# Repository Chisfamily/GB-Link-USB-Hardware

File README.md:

# GB-LINK-USB

**An open-source USB adapter for the Game Boy Link Cable.**

| Top view — v1.4 | Bottom view — v1.4 |
| --- | --- |
|  |  |

*The renders show the current **v1.4** board; the bottom silkscreen reads `GB-Link HW Rev 1.4` with date `20261007`.*

GB-LINK-USB is an RP2040-based hardware adapter that connects original Nintendo
Game Boy, Game Boy Color, and Game Boy Advance systems to a computer over USB.
Together with the open-source
[GBLink-Firmware](https://github.com/GB-Link/GBLink-Firmware), it brings modern
connectivity and community-built tools to original Game Boy hardware.

This hardware was developed with reference to the
[GB-Link-USB-DIY](https://github.com/GB-Link/GB-Link-USB-DIY) project and is
designed to be compatible with the GBLink firmware and its web-based clients.

> [!IMPORTANT]
> The board documented here is hardware **v1.4**. It works with **Game Boy Color
> and Game Boy Advance** (and the original Game Boy) over the Link cable, and it
> adapts the Link-interface power automatically: there is no voltage-selection
> jumper, DIP switch or mechanical switch anywhere on the board.

> [!NOTE]
> GB-LINK-USB is the hardware interface. Available features depend on the
> installed firmware, client software, selected cable, game, and firmware
> version.

## What Can It Do?

With compatible firmware and client software, GB-LINK-USB can provide the
following functions:

| Mode | Description |
| --- | --- |
| **GBA online link** | Bridges two original Game Boy Advance systems over the Internet through a compatible client and server. |
| **Pokémon Gen III trade emulation** | Emulates a GBA link partner for supported Pokémon Generation III trading workflows. |
| **GB/GBC link passthrough** | Transfers Game Boy serial-link data between the console and a computer, enabling supported community clients and online play projects. |
| **Game Boy Printer emulation** | Receives images sent by compatible games so they can be viewed or saved on a computer without an original Game Boy Printer. |
| **Advance Wars link mode** | Supports communication features for *Advance Wars* and *Advance Wars 2*. |
| **Nintendo e-Reader emulation** | Emulates supported Nintendo e-Reader communication workflows. |

Depending on the frontend and firmware version, additional features such as
GBA multiboot transfers may also be available.

The firmware handles the timing-sensitive communication with the console
locally. The computer-side client can then exchange data with another adapter,
an online service, or an emulator without requiring the two consoles to be
connected by one physical Link Cable.

## Hardware Test Photos

The following photos show GB-LINK-USB working with original Game Boy hardware.

### Game Boy Printer Emulation

A Game Boy Color running *Pocket Camera* sends an image through GB-LINK-USB to
the browser-based Game Boy Printer emulator, where the received image can be
previewed and downloaded.

### GBA Multiboot and Cartridge Communication

These tests show a cartridge utility transferred to an original Game Boy
Advance through the Link Cable interface, followed by cartridge-data transfer
between the GBA and the browser client.

| GBA multiboot utility running on original hardware | Cartridge-data transfer through the browser client |
| --- | --- |
|  |  |

## Hardware Features

- Integrated RP2040 microcontroller
- USB Type-C connection
- Game Boy Link interface
- Works with Game Boy Color and Game Boy Advance (and the original Game Boy)
- Bidirectional level translation on all Link lines, including the level-shifted pin 1 line added in v1.4
- Automatic Link-interface power: an on-board TPS2116 power mux selects between the USB 5 V rail and the 3.3 V rail by itself — no jumper, DIP switch or mechanical voltage switch
- Firmware-controlled 3.3 V and 5 V Link-interface reference voltage (no hardware toggle)
- WS2812B RGB status indicator
- BOOTSEL firmware-update support
- SWD programming and debugging connection
- Four-layer, 1.2 mm PCB with an inner ground plane and inner power pours
- Complete KiCad 10 design files
- Manufacturing Gerber package

## Hardware Revision History

| Revision | Status | Summary |
| --- | --- | --- |
| **v1.4** | current | Regulated Link-interface reference with a TPS2116 power mux, level-shifted Link pin 1 line, four-layer PCB |
| **v1.0** | superseded | Two-layer PCB, Link pull-up rail taken from the connected console |

The v1.0 design files are kept under `hw/v1.0/` unchanged for reference.

## Changes in v1.4 (relative to v1.0)

v1.4 is a functional revision of the Game Boy Link interface plus a PCB
stack-up change. The RP2040 core, USB Type-C front end, QSPI flash, crystal,
3.3 V LDO, VBUS diode, status LED, BOOTSEL button, SWD header and the
23.2 mm × 36.05 mm board outline are carried over from v1.0. The USB-C
connector, the Link port and the SWD header keep their exact positions, so the
existing enclosure, Link cables and programming fixtures still fit.

### 1. Link-interface power (main functional change)

In v1.0 the console-side pull-up rail of the four BSS138 level shifters was
`/GBVCC`, which could only be supplied by the connected console through Link
connector pin 1. GPIO11 and GPIO12 were reserved as `/VSWITCH_3V3_PIN` and
`/VSWITCH_5V_PIN`, but no switching hardware was fitted, so the interface
level could not actually be selected.

In v1.4 that rail is generated on-board as `/LINK_VREF` by a TPS2116 power
mux, and firmware can select the interface level:

| Item | v1.0 | v1.4 |
| --- | --- | --- |
| Console-side pull-up rail | `/GBVCC`, taken from Link connector pin 1 | `/LINK_VREF`, generated by U4 |
| Voltage source | fixed, supplied by the console | U4 **TPS2116DRL** power mux: `VIN1` = `+3V3`, `VIN2` = `VIN` (VBUS after D1), `VOUT` = `/LINK_VREF` |
| Level control | none (reserved nets only) | GPIO11 → U2 **74LVC1G04GV** inverter → U4 `MODE`; GPIO12 → U4 `PR1` |
| Power-up state | — | R11 and R14 (10 kΩ) pull GPIO11 and GPIO12 high, so `MODE` idles low |
| `/LINK_VREF` load | — | R20, 4.7 kΩ to GND |
| Decoupling | — | C18 1 µF on `/LINK_VREF`, C19 100 nF on `+3V3`, C17 1 µF and C20 10 µF on `VIN` |
| U4 `ST` status output | — | not connected |

Practical effect: the Link interface no longer depends on the console or cable
delivering power on pin 1, and the console-facing bus runs at 3.3 V or 5 V
depending on the GPIO11/GPIO12 setting instead of always following the console.
Firmware has to drive GPIO11 and GPIO12 for the selection to take effect.

The source selection itself is automatic and needs no user action: the board
carries no voltage-select jumper, DIP switch or mechanical switch, so a single
board covers both the Game Boy Color and the Game Boy Advance without
reconfiguration.

### 2. Link connector pin 1

| Item | v1.0 | v1.4 |
| --- | --- | --- |
| Net on J1 pin 1 | `/GBVCC` | `/LINK_PIN1` |
| Function | pull-up rail for R2, R4, R8, R10 only, no MCU connection | fifth level-translated Link channel on GPIO4 |
| Level shifter | — | Q5 **BSS138**, gate to `+3V3`, R12 10 kΩ on the 3.3 V side, R13 10 kΩ to `/LINK_VREF` on the Link side |
| Pull-ups R2, R4, R8, R10 | to `/GBVCC` | to `/LINK_VREF` |

GPIO4 was labelled `/SD2` and left unused in v1.0; it is now `/GP4` and
drives the added level-translation channel through Q5.

### 3. Schematic net changes

| Removed in v1.4 | Added in v1.4 |
| --- | --- |
| `/GBVCC`, `/SD2`, `/VSWITCH_3V3_PIN`, `/VSWITCH_5V_PIN` | `/LINK_VREF`, `/LINK_PIN1`, `/GP4`, `/GP11`, `/GP12`, `Net-(U4-MODE)` |

Net count: 62 in v1.0, 66 in v1.4. The schematic drawing sheet changed from A4
to A3 to fit the added circuitry; the design notes and the RP2040 reference
circuits are unchanged.

### 4. Bill of materials

| Reference | Change |
| --- | --- |
| U4 | added — TPS2116DRL power mux, SOT-583-8 |
| U2 | added — 74LVC1G04GV inverter, SOT-23-5 |
| Q5 | added — BSS138 level shifter, SOT-23-3 |
| R11, R14 | added — 10 kΩ pull-ups on the GPIO11/GPIO12 control lines |
| R12, R13 | added — 10 kΩ level-shifter pull-ups for the pin 1 line |
| R20 | added — 4.7 kΩ load on `/LINK_VREF` |
| C17, C18 | added — 1 µF, 0402 |
| C19 | added — 100 nF, 0402 |
| C20 | added — 10 µF, 0603 |
| C1, C2, C7, C8 | 1 µF parts moved from 0603 to 0402 |
| C3–C6, C9–C15 | footprint reference changed from the local `Library:` library to `Capacitor_SMD:`, pad geometry unchanged |
| OSHW logo footprint | enlarged from 5.7 mm × 6 mm to 11.4 mm × 12 mm |

No component was removed and no value changed other than the C1, C2, C7 and C8
package sizes. The BOM grew from 19 to 23 line items and from 45 to 57
placements.

### 5. PCB and fabrication

| Item | v1.0 | v1.4 |
| --- | --- | --- |
| Copper layers | 2 (`F.Cu`, `B.Cu`) | 4 (`F.Cu`, `In1.Cu`, `In2.Cu`, `B.Cu`) |
| Inner layers | — | `In1.Cu` continuous ground plane; `In2.Cu` power pours for `+3V3` and `+1V1` |
| Ground pours | `F.Cu` and `B.Cu` | `F.Cu`, `B.Cu` and `In1.Cu` |
| Board outline | 23.2 mm × 36.05 mm | unchanged |
| Board thickness | 1.2 mm | 1.2 mm |
| Footprints / pads | 48 / 200 | 60 / 234 |
| Track segments | 289 | 405 |
| Vias | 64 (52 × 0.5/0.3 mm, 12 × 0.4/0.15 mm) | 89 (all 0.5/0.3 mm) |
| Minimum track width | 0.1524 mm | 0.1524 mm, plus a new 0.1778 mm class |
| Copper zones | 13 | 51 |
| Nets | 62 | 66 |
| Bottom-side silkscreen | OSHW logo | OSHW logo, enlarged |
| Board marking | `GB-Link-USB HW Rev 1.0` | `GB-Link HW Rev 1.4` and date `20261007` |

The move to four layers adds a solid ground plane directly under the RP2040 and
the USB differential pair, plus `+3V3` and `+1V1` pours on `In2.Cu`. The
vias also moved from the v1.0 mix of 0.4/0.15 mm and 0.5/0.3 mm to 0.5/0.3 mm
only, which is a less aggressive drill process for low-cost fabrication.

### 6. Unchanged

RP2040 and its QSPI flash, 12 MHz crystal and load network, AP2112K-3.3 LDO,
1N5819WS VBUS diode, USB-C receptacle with its 5.1 kΩ CC resistors and 27 Ω
series resistors, level shifters Q1–Q4 with their 3.3 V-side pull-ups,
WS2812B indicator, BOOTSEL button and pull-up, RUN/reset button, SWD header,
Link port footprint with pins J1.2–J1.5, and the 1.2 mm, 23.2 mm × 36.05 mm
board outline.

## Supported Firmware

The recommended firmware is:

- [GBLink-Firmware](https://github.com/GB-Link/GBLink-Firmware)

The firmware turns the RP2040 into a USB-to-Game Boy Link Cable adapter and
provides the protocol modes used by the GB-Link web clients.

Firmware and browser tools are maintained separately from this hardware
repository. Visit the following pages for current releases and client
instructions:

- [GB-Link Launcher](https://launcher.gblink.io/)
- [GBLink-Firmware releases](https://github.com/GB-Link/GBLink-Firmware/releases)

## Community

Questions, build photos, firmware tips and community-made tools are discussed on
the GB-Link Discord server:

- **Discord:** <https://discord.gg/2MPprnMmg>

When asking about a hardware problem, please include the board revision
(v1.0 or v1.4), the console model (GB / GBC / GBA), the cable type and a photo
of the board. Those four details solve most issues in the first reply.

## Quick Start

1. Manufacture and assemble the PCB using the files in this repository, or use
   an already assembled GB-LINK-USB board.
2. Install the latest GBLink firmware:
   - Use the [GB-Link Launcher](https://launcher.gblink.io/) for web-based
     flashing and updates; or
   - Download `gblink.uf2` from the
     [firmware releases](https://github.com/GB-Link/GBLink-Firmware/releases),
     hold the board's BOOTSEL button while connecting it to the computer, and
     copy the UF2 file to the RP2040 drive.
3. Connect the Game Boy system to the adapter with a compatible Link Cable.
4. Open the GB-Link Launcher, select the required mode, and follow the
   instructions for the game or client you want to use.

## Cable Compatibility

Cable construction differs between Game Boy generations and manufacturers.
According to the GBLink-Firmware documentation:

- A fully wired generic GBC Link Cable can support both GB/GBC and GBA modes.
- An original GBA Link Cable is intended for GBA modes only.
- For GBA operation, the adapter must be connected to the master side of the
  GBA cable.
- Some low-cost third-party GBA cables omit required conductors and may cause
  unreliable communication.

Always confirm the cable selection in the client before starting a link mode.

## Repository Structure

```text
.
|-- hw/
|   |-- v1.0/                    Superseded revision: KiCad schematic, PCB, libraries, 3D models
|   `-- v1.4/                    Current revision: KiCad schematic, PCB, schematic PDF, libraries
|-- gerber/
|   `-- GB-LINK-USB-V1.0-20260827.zip
|                                Manufacturing package for the v1.0 board
|-- extras/
|   |-- gb-link-usb-top.png      Top-side render of the v1.4 board
|   |-- gb-link-usb-bot.png      Bottom-side render of the v1.4 board
|   |-- gbc.jpg                  Game Boy Printer emulation test
|   |-- gba1.jpg                 GBA multiboot test
|   `-- gba2.jpg                 GBA cartridge-data transfer test
`-- README.md
```

## Manufacturing Notes

- Current hardware revision: **v1.4**
- PCB layer count: **4 layers** (outer signal, inner ground plane and power pours)
- PCB thickness: **1.2 mm**
- Board outline: **23.2 mm × 36.05 mm**, unchanged from v1.0
- KiCad project:
  [`hw/v1.4/GB-LINK-v1.4.kicad_pro`](hw/v1.4/GB-LINK-v1.4.kicad_pro)
- Schematic PDF:
  [`hw/v1.4/GB-LINK-v1.4.pdf`](hw/v1.4/GB-LINK-v1.4.pdf)
- Gerber package in `gerber/` is generated from the **v1.0** design; export
  fresh fabrication output from `hw/v1.4/GB-LINK-v1.4.kicad_pcb` before
  ordering v1.4 boards.

Before ordering assembled boards, review the schematic, PCB, component
availability, connector orientation, and fabrication outputs for the selected
manufacturer. Hardware is provided without warranty; build and use it at your
own risk.

## Acknowledgements

This project exists because many people chose to share their hardware designs,
firmware, documentation, testing, and knowledge with the community.

Special thanks to:

- The [GB-Link-USB-DIY](https://github.com/GB-Link/GB-Link-USB-DIY) project for
  the open hardware reference design and manufacturing documentation.
- [agtbaskara](https://github.com/agtbaskara/game-boy-pico-link-board), creator
  of the original Game Boy Pico link-board design.
- [fairy0715](https://github.com/fairy0715/game-boy-pico-link-board-with-gbaport)
  for the Link Port version on which later designs were based.
- The [GB-Link](https://github.com/GB-Link) maintainers and every contributor to
  [GBLink-Firmware](https://github.com/GB-Link/GBLink-Firmware).
- The [Celio-Link](https://github.com/Celio-Link/Celio-Firmware) project and its
  contributors, whose work forms an important part of the firmware's history.
- Everyone who has contributed code, hardware layouts, footprints, client
  software, documentation, issue reports, testing, and ideas to the wider
  Game Boy homebrew community.

Thank you to all of these open-source contributors. Your work keeps classic
hardware useful, accessible, and fun for a new generation of players and
developers.

## Disclaimer

This is an unofficial, community-developed open hardware project. It is not
affiliated with, endorsed by, or licensed by Nintendo, The Pokémon Company, or
any related game publisher. Game Boy, Game Boy Color, Game Boy Advance, Pokémon,
and other product names are trademarks of their respective owners.

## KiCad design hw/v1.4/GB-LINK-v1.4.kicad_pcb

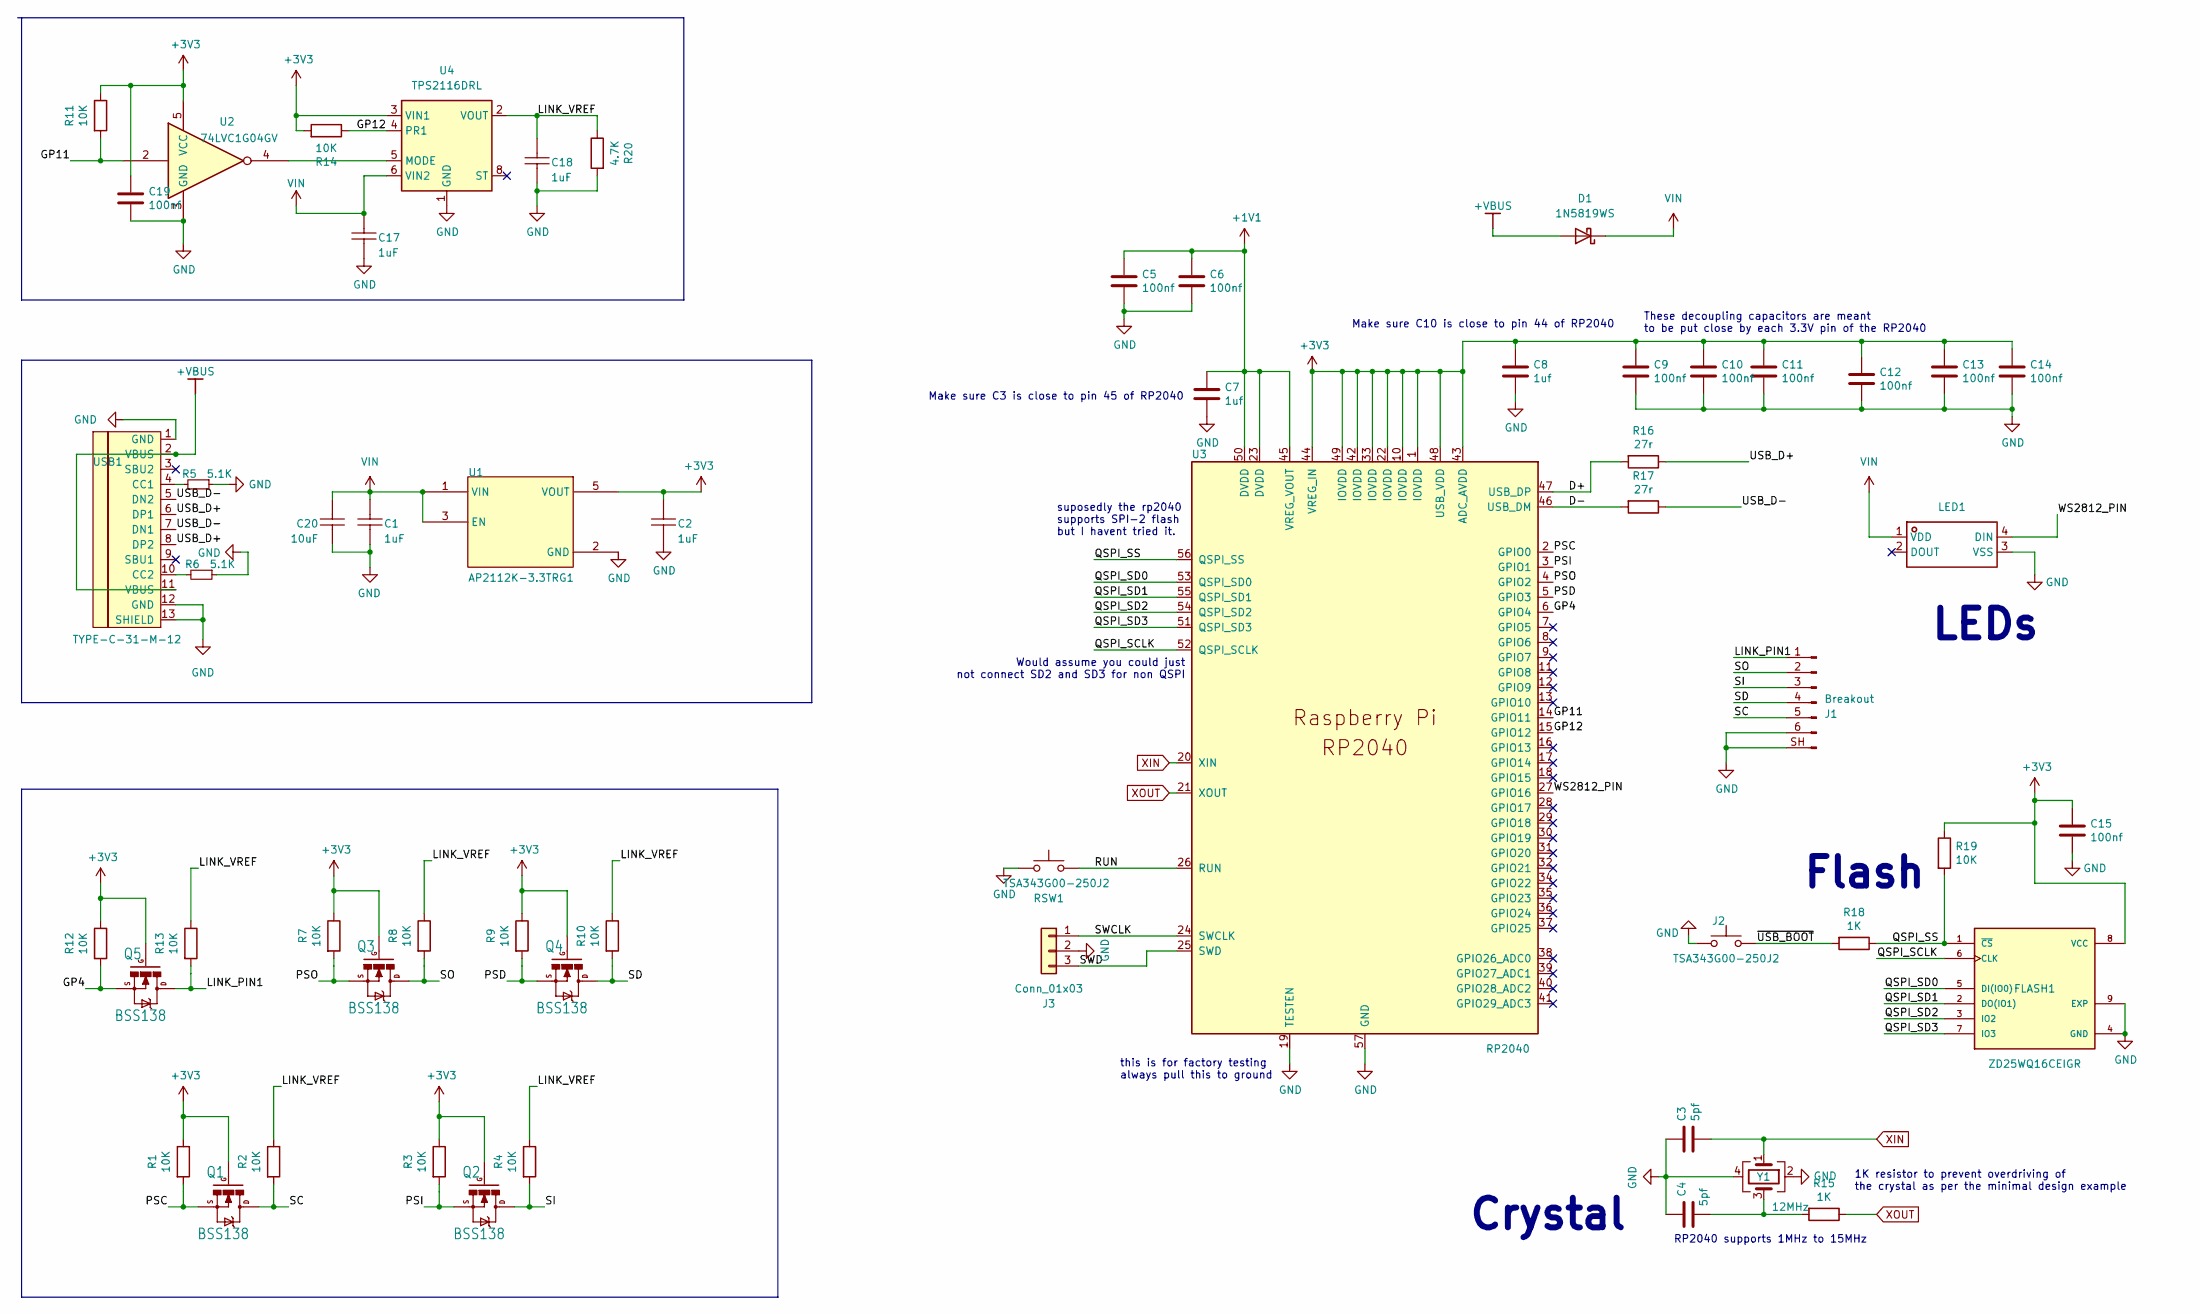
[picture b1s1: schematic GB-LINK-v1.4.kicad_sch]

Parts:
C1, C2, C17, C18: 1uF; C_0402_1005Metric; TOLERANCE 10%; VOLTAGE RATING 25V; MANUFACTURER PART NUMBER C1005X5R1E105K050BC
C3, C4: 5pf; C_0402_1005Metric
C5, C6, C9, C10, C11, C12, C13, C14, C15, C19: 100nf; C_0402_1005Metric
C7, C8: 1uf; C_0402_1005Metric
C20: 10uF; C_0603_1608Metric; TOLERANCE 10%; VOLTAGE RATING 25V; MANUFACTURER PART NUMBER C1005X5R1E105K050BC
D1: 1N5819WS; D_SOD-323
FLASH1: ZD25WQ16CEIGR; Winbond_USON-8-1EP_3x2mm_P0.5mm_EP0.2x1.6mm
J1: Breakout; gba_linkport
J2: TSA343G00-250J2; SW_Push_SPST_NO_Alps_SKRK
J3: Conn_01x03; PinHeader_1x03_P2.00mm_Vertical
LED1: LED_WS2812B-Mini_PLCC4_3.5x3.5mm
Q1, Q2, Q3, Q4, Q5: BSS138; SOT-23-3
R1, R2, R3, R4, R7, R8, R9, R10, R11, R12, R13, R14, R19: 10K; R_0402_1005Metric
R5, R6: 5.1K; R_0402_1005Metric
R15, R18: 1K; R_0402_1005Metric
R16, R17: 27r; R_0402_1005Metric
R20: 4.7K; R_0402_1005Metric
RSW1: TSA343G00-250J2; SW_Push_SPST_NO_Alps_SKRK
U1: AP2112K-3.3TRG1; SOT-23-5; DROPOUT VOLTAGE 250mV; OUTPUT VOLTAGE 3.3V; MANUFACTURER PART NUMBER AP2112K-3.3TRG1
U2: 74LVC1G04GV; SOT-23-5
U3: RP2040; RP2040-QFN-56; LCSC C2040
U4: TPS2116DRL; SOT-583-8
USB1: TYPE-C-31-M-12; HRO-TYPE-C-31-M-12; LCSC C165948
Y1: 12MHz; Crystal_SMD_3225-4Pin_3.2x2.5mm

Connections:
+1V1: C5.1, C6.1, C7.1, U3.23 (DVDD), U3.45 (VREG_VOUT), U3.50 (DVDD)
+3V3: C2.2, C8.1, C9.1, C10.1, C11.1, C12.1, C13.1, C14.1, C15.1, C19.1, FLASH1.8 (VCC), Q1.1 (G), Q2.1 (G), Q3.1 (G), Q4.1 (G), Q5.1 (G), R1.1, R3.1, R7.1, R9.1, R11.1, R12.1, R14.2, R19.1, U1.5 (VOUT), U2.5 (VCC), U3.1 (IOVDD), U3.10 (IOVDD), U3.22 (IOVDD), U3.33 (IOVDD), U3.42 (IOVDD), U3.43 (ADC_AVDD), U3.44 (VREG_IN), U3.48 (USB_VDD), U3.49 (IOVDD), U4.3 (VIN1)
+VBUS: D1.2 (A), USB1.2 (VBUS), USB1.11 (VBUS)
/D+: R16.2, U3.47 (USB_DP)
/D-: R17.2, U3.46 (USB_DM)
/GP4: Q5.2 (S), R12.2, U3.6 (GPIO4)
/GP11: R11.2, U2.2, U3.14 (GPIO11)
/GP12: R14.1, U3.15 (GPIO12), U4.4 (PR1)
/LINK_PIN1: J1.1, Q5.3 (D), R13.2
/LINK_VREF: C18.2, R2.1, R4.1, R8.1, R10.1, R13.1, R20.1, U4.2 (VOUT), U4.7 (VOUT)
/PSC: Q1.2 (S), R1.2, U3.2 (GPIO0)
/PSD: Q4.2 (S), R9.2, U3.5 (GPIO3)
/PSI: Q2.2 (S), R3.2, U3.3 (GPIO1)
/PSO: Q3.2 (S), R7.2, U3.4 (GPIO2)
/QSPI_SCLK: FLASH1.6 (CLK), U3.52 (QSPI_SCLK)
/QSPI_SD0: FLASH1.5 (DI(IO0)), U3.53 (QSPI_SD0)
/QSPI_SD1: FLASH1.2 (DO(IO1)), U3.55 (QSPI_SD1)
/QSPI_SD2: FLASH1.3 (IO2), U3.54 (QSPI_SD2)
/QSPI_SD3: FLASH1.7 (IO3), U3.51 (QSPI_SD3)
/QSPI_SS: FLASH1.1 (~CS), R18.1, R19.2, U3.56 (QSPI_SS)
/RUN: RSW1.2, U3.26 (RUN)
/SC: J1.5, Q1.3 (D), R2.2
/SD: J1.4, Q4.3 (D), R10.2
/SI: J1.3, Q2.3 (D), R4.2
/SO: J1.2, Q3.3 (D), R8.2
/SWCLK: J3.1, U3.24 (SWCLK)
/SWD: J3.3, U3.25 (SWD)
/USB_D+: R16.1, USB1.6 (DP1), USB1.8 (DP2)
/USB_D-: R17.1, USB1.5 (DN2), USB1.7 (DN1)
/WS2812_PIN: LED1.4 (DIN), U3.27 (GPIO16)
/~USB_BOOT: J2.1, R18.2
GND: C1.1, C2.1, C3.1, C4.1, C5.2, C6.2, C7.2, C8.2, C9.2, C10.2, C11.2, C12.2, C13.2, C14.2, C15.2, C17.1, C18.1, C19.2, C20.1, FLASH1.4 (GND), FLASH1.9 (EXP), J1.6, J1.SH (Pin_7), J2.2, J3.2, LED1.3 (VSS), R5.1, R6.1, R20.2, RSW1.1, U1.2 (GND), U2.3 (GND), U3.19 (TESTEN), U3.57 (GND), U4.1 (GND), USB1.1 (GND), USB1.12 (GND), USB1.13 (SHIELD), Y1.2, Y1.4
unnamed: C4.2, R15.2, Y1.3
unnamed: U2.4, U4.5 (MODE)
unnamed: R5.2, USB1.4 (CC1)
unnamed: R6.2, USB1.10 (CC2)
VIN: C1.2, C17.2, C20.2, D1.1 (K), LED1.1 (VDD), U1.1 (VIN), U1.3 (EN), U4.6 (VIN2)
XIN: C3.2, U3.20 (XIN), Y1.1
XOUT: R15.1, U3.21 (XOUT)

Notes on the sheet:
These decoupling capacitors are meant to be put close by each 3.3V pin of the RP2040
this is for factory testing always pull this to ground
suposedly the rp2040 supports SPI-2 flash but I havent tried it.
1K resistor to prevent overdriving of the crystal as per the minimal design example
LEDs
Crystal
Flash
RP2040 supports 1MHz to 15MHz
Make sure C3 is close to pin 45 of RP2040
Make sure C10 is close to pin 44 of RP2040
Would assume you could just not connect SD2 and SD3 for non QSPI

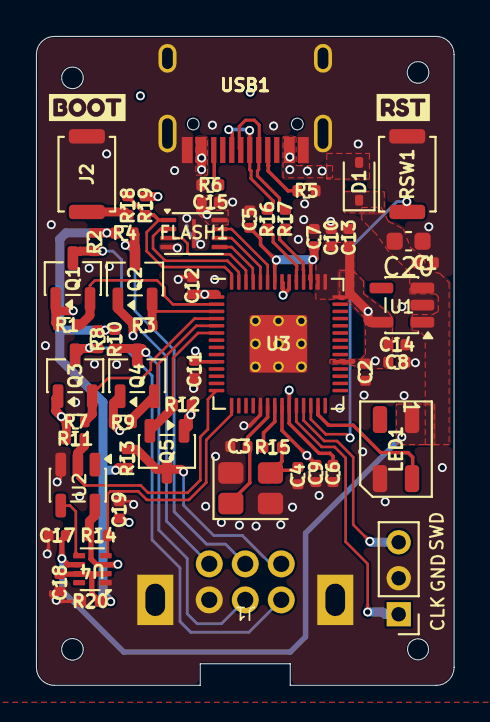
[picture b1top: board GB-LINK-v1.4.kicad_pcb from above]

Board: 4 copper layers, 23.2 x 36.0 mm, 59 parts (0 on the bottom side), 39 nets.

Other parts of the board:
kibuzzard-6A85AEF8: G***; kibuzzard-6A85AEF8
kibuzzard-6A85AF09: G***; kibuzzard-6A85AF09
